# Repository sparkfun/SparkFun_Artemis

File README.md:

SparkFun Artemis
============================

[*SparkFun Artemis Module (WRL-15484)*](https://www.sparkfun.com/products/15484)

The Artemis Module from SparkFun is the first product to bridge the market between hobbyists and consumer products. We've exhaustively packaged all the power of a modern microcontroller into a module that is both extremely easy to use but is mass-market ready. 

The flexibility of the Artemis module starts with our [Arduino core](https://github.com/sparkfun/Arduino_Apollo3). You can program and use the Artemis module just like you would an Uno or any other Arduino. Time to first blink is just 5 minutes away! We built the core from the ground up, making it fast and as light weight as possible. 

Next is the module itself. Measuring 10x15mm the Artemis module has all the support circuitry you need to use the fantastic Apollo3 processor in your next project. We're proud to say the SparkFun Artemis module is the first open source hardware module with the design files freely and easily available here (on this repo). We've carefully designed the module so that routing to the module can be done with low-cost 2-layer PCBs with 8mil trace/space. Addtionally, we've released four open-source-hardware example products that act as a starting point for your product.

Made in the USA at SparkFun's Boulder production line the Artemis module is designed for consumer grade products. This truly differentiates the Artemis from its Arduino brethren. Ready to scale your product? The Artemis will grow with you beyond the Uno footprint and Arduino IDE. Tape and reel quantities or the Artemis module are available in addition, the Artemis has an advanced HAL (hardware abstraction layer) allowing users to push the modern Cortex-M4F architecture to its limit. 

This repo contains the design files for the 4-layer PCB. This design is pretty reliant on sophisticated manufacturing tools. We *do not* recommend that you order PCBs and attempt to hand stencil or hand place these components. We hope you can learn from our work and share what you've learned for the next generation of engineers and hackers. 

Repository Contents
-------------------
* **/Artwork** - SVG of laser etching on RF shield
* **/Bootloader** - Tools for loading the Artemis with Ambiq's secure bootloader
* **/Documentation** - Data sheets, additional product information
* **/Hardware** - Eagle design files (.brd, .sch)

Documentation
-------------------
* **[Designing with the SparkFun Artemis](https://learn.sparkfun.com/tutorials/designing-with-the-sparkfun-artemis)** - Layout and design considerations when using the Artemis module.
* **[Artemis Development with Arduino](https://learn.sparkfun.com/tutorials/artemis-development-with-arduino)** - Introduction to the Arduino core for the Artemis Module.
* **[Using SparkFun Edge Board with Ambiq Apollo3 SDK](https://learn.sparkfun.com/tutorials/using-sparkfun-edge-board-with-ambiq-apollo3-sdk)** - Getting set up with the Apollo3 Software Development Kit.

License Information
-------------------

This product is _**open source**_! 

Please review the LICENSE.md file for license information. 

If you have any questions or concerns on licensing, please contact techsupport@sparkfun.com.

Please use, reuse, and modify these files as you see fit. Please maintain attribution to SparkFun Electronics and release any derivative under the same license.

Distributed as-is; no warranty is given.

- Your friends at SparkFun.

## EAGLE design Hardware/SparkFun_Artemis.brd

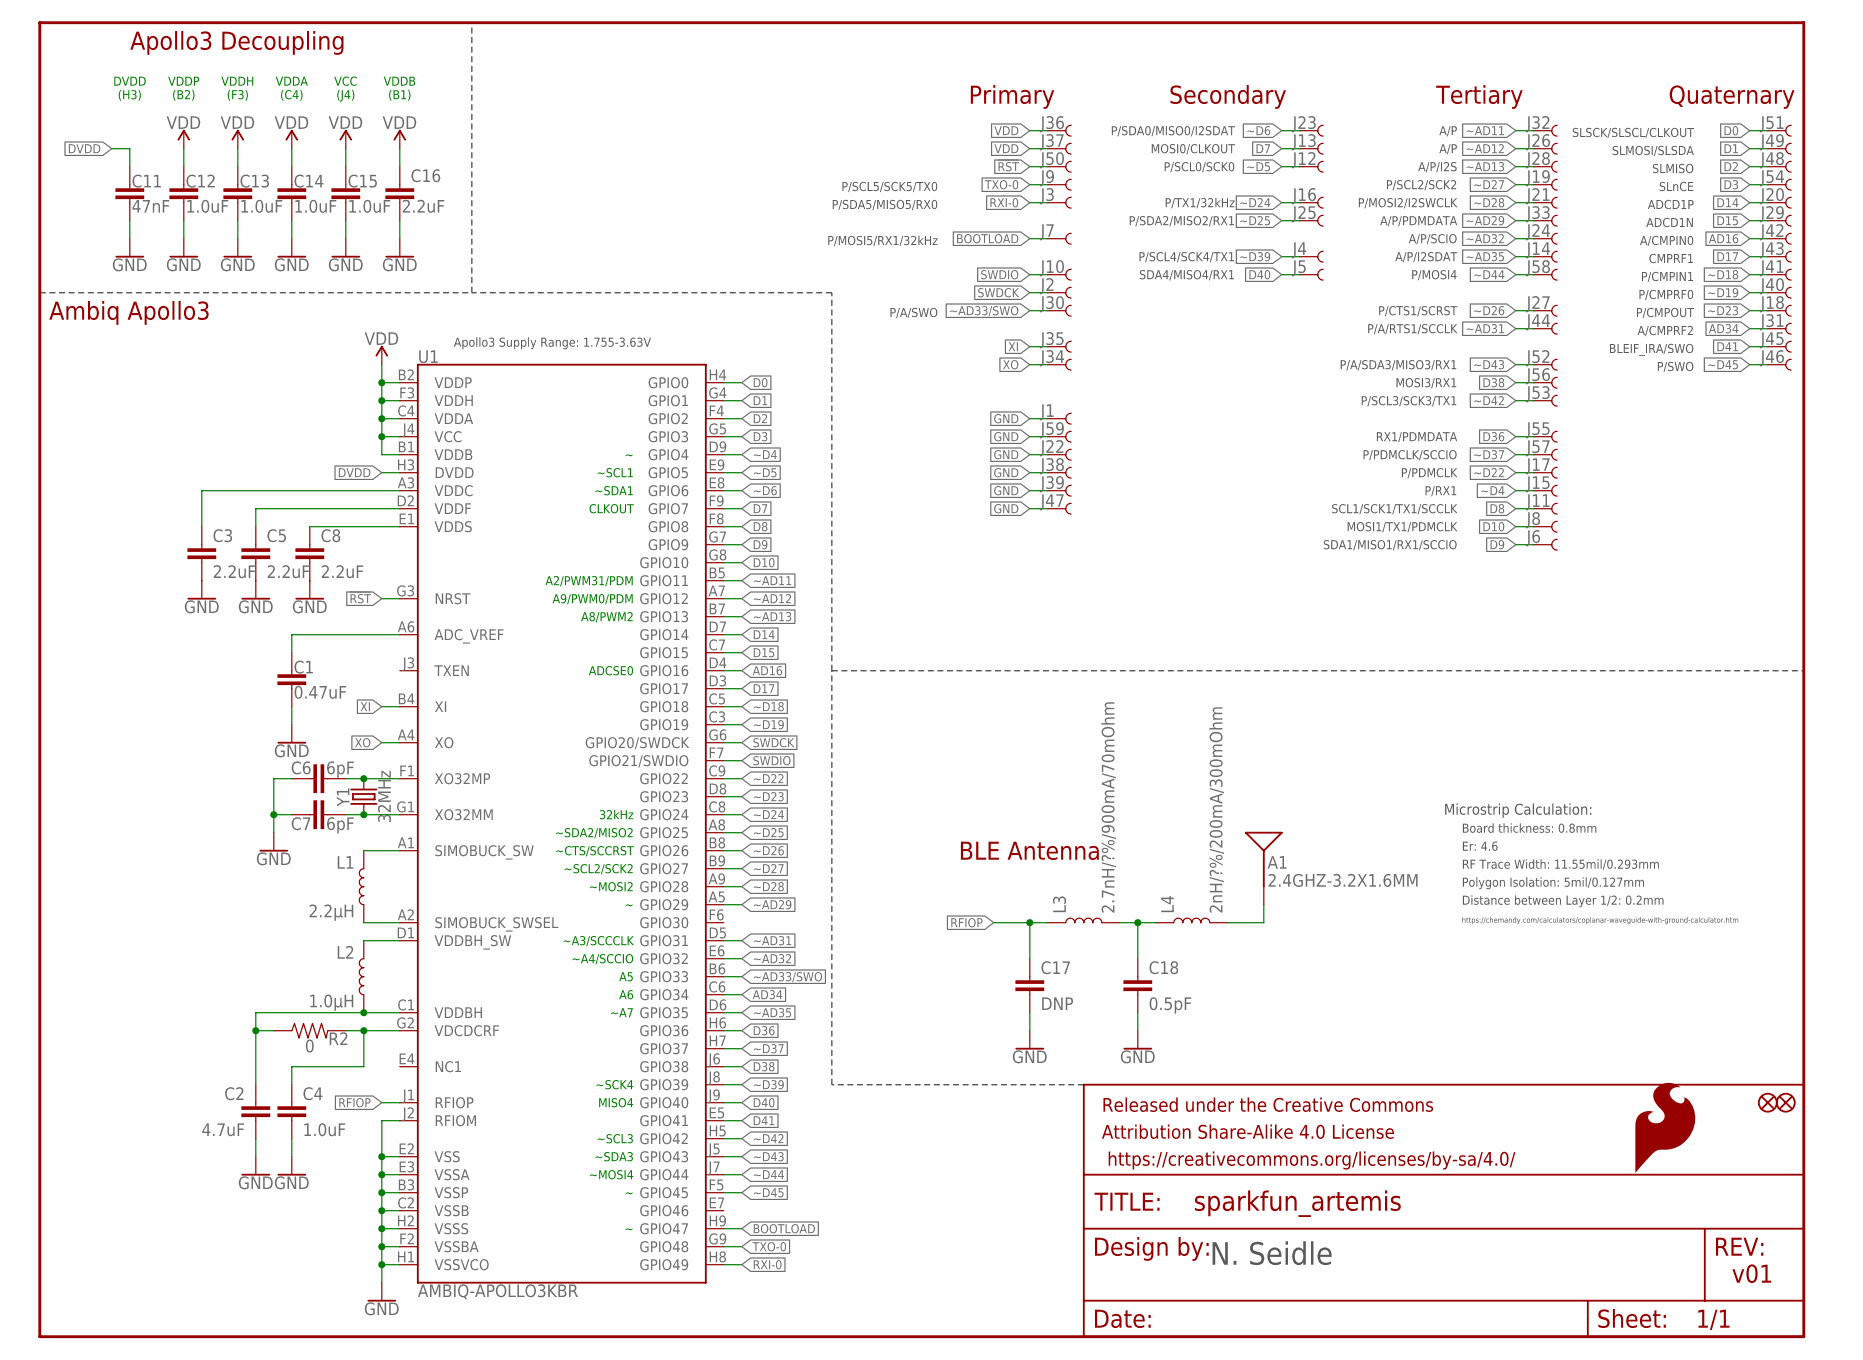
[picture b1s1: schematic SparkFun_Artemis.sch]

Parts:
A1: 2.4GHZ-3.2X1.6MM; ANT-2.4GHZ-8.0X1.0MM
C1: 0.47uF; 0402-TIGHT
C2: 4.7uF; 0402-TIGHT
C3, C5, C8, C16: 2.2uF; 0402-TIGHT
C4, C12, C13, C14, C15: 1.0uF; 0402-TIGHT
C6, C7: 6pF; 0402-TIGHT
C11: 47nF; 0402-TIGHT
C17: DNP; 0402-TIGHT
C18: 0.5pF; 0402-TIGHT
FD3, FD4: FIDUCIAL0.2MM; FIDUCIAL-0.2MM
FRAME1: FRAME-LETTER; CREATIVE_COMMONS
J1, J2, J3, J4, J5, J6, J7, J8, J9, J10, J11, J12, J13, J14, J15, J16, J17, J18, J19, J20, J21, J23, J24, J25, J26, J27, J28, J29, J30, J31, J32, J33, J34, J35, J36, J37, J39, J40, J41, J42, J43, J44, J45, J46, J47, J48, J49, J50, J51, J52, J53, J54, J55, J56, J57, J58, J59: PAD.4X.6; MODULE_PAD
J22, J38: PAD.35X.35; MODULE_MINI_PAD
L1: 2.2μH; 0805-WIDE
L2: 1.0μH; 0805-WIDE
L3: 2.7nH/?%/900mA/70mOhm; 0402-TIGHT
L4: 2nH/?%/200mA/300mOhm; 0402-TIGHT
LOGO1: SFE_LOGO_FLAME.05_INCH_INTERNAL; SFE_LOGO_FLAME_INTERNAL_0.05
R2: 0; 0402-TIGHT
U1: AMBIQ-APOLLO3KBR; BGA-81-5X5MM
Y1: 32MHz; CRYSTAL-SMD-2.0X1.6MM

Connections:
!RST: J50.1, U1.G3 (NRST)
AD16: J42.1, U1.D4 (GPIO16)
AD34: J31.1, U1.C6 (GPIO34)
ADC_VREF: C1.1, U1.A6 (ADC_VREF)
BOOTLOAD: J7.1, U1.H9 (GPIO47)
D0: J51.1, U1.H4 (GPIO0)
D1: J49.1, U1.G4 (GPIO1)
D2: J48.1, U1.F4 (GPIO2)
D3: J54.1, U1.G5 (GPIO3)
D7: J13.1, U1.F9 (GPIO7)
D8: J11.1, U1.F8 (GPIO8)
D9: J6.1, U1.G7 (GPIO9)
D10: J8.1, U1.G8 (GPIO10)
D14: J20.1, U1.D7 (GPIO14)
D15: J29.1, U1.C7 (GPIO15)
D17: J43.1, U1.D3 (GPIO17)
D36: J55.1, U1.H6 (GPIO36)
D38: J56.1, U1.J6 (GPIO38)
D40: J5.1, U1.J9 (GPIO40)
D41: J45.1, U1.E5 (GPIO41)
DVDD: C11.1, U1.H3 (DVDD)
GND: C1.2, C2.2, C3.2, C4.2, C5.2, C6.1, C7.1, C8.2, C11.2, C12.2, C13.2, C14.2, C15.2, C16.2, C17.2, C18.2, J1.1, J22.1, J38.1, J39.1, J47.1, J59.1, U1.B3 (VSSP), U1.C2 (VSSB), U1.E2 (VSS), U1.E3 (VSSA), U1.F2 (VSSBA), U1.H1 (VSSVCO), U1.H2 (VSSS), U1.J2 (RFIOM)
unnamed: A1.FEED, L4.2
unnamed: C7.2, U1.G1 (XO32MM), Y1.1
unnamed: C6.2, U1.F1 (XO32MP), Y1.3 (2)
unnamed: C18.1, L3.2, L4.1
RFIOP: C17.1, L3.1, U1.J1 (RFIOP)
RXI-0: J3.1, U1.H8 (GPIO49)
SIMBUCK_SWSEL: L1.2, U1.A2 (SIMOBUCK_SWSEL)
SIMOBUCK_SW: L1.1, U1.A1 (SIMOBUCK_SW)
SWDCK: J2.1, U1.G6 (GPIO20/SWDCK)
SWDIO: J10.1, U1.F7 (GPIO21/SWDIO)
TXO-0: J9.1, U1.G9 (GPIO48)
VDCDCRF: C4.1, R2.2, U1.G2 (VDCDCRF)
VDD: C12.1, C13.1, C14.1, C15.1, C16.1, J36.1, J37.1, U1.B1 (VDDB), U1.B2 (VDDP), U1.C4 (VDDA), U1.F3 (VDDH), U1.J4 (VCC)
VDDBH: C2.1, L2.2, R2.1, U1.C1 (VDDBH)
VDDBH_SW: L2.1, U1.D1 (VDDBH_SW)
VDDC: C3.1, U1.A3 (VDDC)
VDDF: C5.1, U1.D2 (VDDF)
VDDS: C8.1, U1.E1 (VDDS)
XI: J35.1, U1.B4 (XI)
XO: J34.1, U1.A4 (XO)
~AD11: J32.1, U1.B5 (GPIO11)
~AD12: J26.1, U1.A7 (GPIO12)
~AD13: J28.1, U1.B7 (GPIO13)
~AD29: J33.1, U1.A5 (GPIO29)
~AD31: J44.1, U1.D5 (GPIO31)
~AD32: J24.1, U1.E6 (GPIO32)
~AD33/SWO: J30.1, U1.B6 (GPIO33)
~AD35: J14.1, U1.D6 (GPIO35)
~D4: J15.1, U1.D9 (GPIO4)
~D5: J12.1, U1.E9 (GPIO5)
~D6: J23.1, U1.E8 (GPIO6)
~D18: J41.1, U1.C5 (GPIO18)
~D19: J40.1, U1.C3 (GPIO19)
~D22: J17.1, U1.C9 (GPIO22)
~D23: J18.1, U1.D8 (GPIO23)
~D24: J16.1, U1.C8 (GPIO24)
~D25: J25.1, U1.A8 (GPIO25)
~D26: J27.1, U1.B8 (GPIO26)
~D27: J19.1, U1.B9 (GPIO27)
~D28: J21.1, U1.A9 (GPIO28)
~D37: J57.1, U1.H7 (GPIO37)
~D39: J4.1, U1.J8 (GPIO39)
~D42: J53.1, U1.H5 (GPIO42)
~D43: J52.1, U1.J5 (GPIO43)
~D44: J58.1, U1.J7 (GPIO44)
~D45: J46.1, U1.F5 (GPIO45)

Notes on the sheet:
DVDD (H3)
VDDP (B2)
VDDH (F3)
VDDA (C4)
VCC (J4)
VDDB (B1)
ADCSE0
A2/PWM31/PDM
~A3/SCCCLK
~SCL3
~SDA3
~A4/SCCIO
~A7
v01
Apollo3 Supply Range: 1.755-3.63V
Ambiq Apollo3
Apollo3 Decoupling
BLE Antenna
A9/PWM0/PDM
A8/PWM2
~CTS/SCCRST
~SDA2/MISO2
~SCL2/SCK2
~MOSI2
~MOSI4
Primary
Secondary
Tertiary
~SCL1
~SDA1
CLKOUT
32kHz
~SCK4
MISO4
N. Seidle
Distance between Layer 1/2: 0.2mm
Microstrip Calculation:
Board thickness: 0.8mm
Er: 4.6
RF Trace Width: 11.55mil/0.293mm

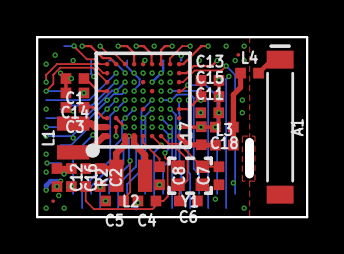
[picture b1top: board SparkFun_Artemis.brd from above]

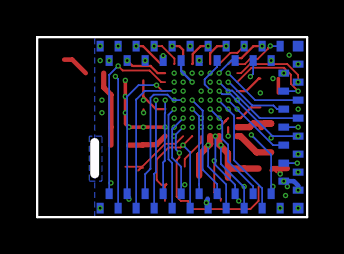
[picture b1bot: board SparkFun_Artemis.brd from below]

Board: 4 copper layers, 15.0 x 10.0 mm, 87 parts (59 on the bottom side), 68 nets.

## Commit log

2019-03-27 Adding docs
2019-03-27 Routing done
2019-03-27 Moar pins
2019-03-28 Add C9 pad. Add FP for Artemis module.
2019-03-28 Fix pad slightly off center.
2019-03-29 Moving pads to bDocu. Changing layer colors.
2019-03-30 Changing RF trace width to 11.55mil
2019-04-04 Change chip antenna. Fixed shield running into trace. Post design review.
2019-04-15 Antenna change
2019-04-15 Going to buried vias
2019-04-16 Buried via approach. Moar GPIOs!
2019-04-16 Commit for Quote
2019-04-17 Add fiducials. Add auto-bootload timing diagram.
2019-04-17 Submitting for production
2019-04-18 Adding new v1 FP of Artemis module
2019-05-13 Update inductor part # to 1mm height
2019-05-21 Add bootloader binary
2019-05-28 Adding dimensions
2019-05-28 Add antenna datasheet. Remove old datasheets.
2019-06-05 Add readme. Clean up repo.
2019-06-05 Compress schematic
2019-06-11 Adding 115200 bootloader bin and tools.
2019-06-14 Changing timeouts on bootloader bins. See readme notes. Was failing at 115200.
2019-06-15 Removing old bootload files. Adding Artemis Bootloader v1.
2019-08-07 Remove old bootloader files. Update readme to describe new auto bootloader.
2019-08-07 Update to v3 SVL bootloader
2020-01-24 Add v10 datasheet
2020-07-21 Update SVL to v5
2020-07-21 Fix broken links. Add info for GUI and original SVL code.
2026-03-07 Add 3D models of the module
    Got this 3D model on the SparkFun forums. Thanks TS-Russel. Wanted to share
    Also I made an STL version for broader compatibility

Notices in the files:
parts and their libraries:
SparkFun-Aesthetics: Licensing: Creative Commons ShareAlike 4.0 International - https://creativecommons.org/licenses/by-sa/4.0
SparkFun-Aesthetics: Released under the Creative Commons Attribution Share-Alike 4.0 License
SparkFun-Aesthetics: https://creativecommons.org/licenses/by-sa/4.0
